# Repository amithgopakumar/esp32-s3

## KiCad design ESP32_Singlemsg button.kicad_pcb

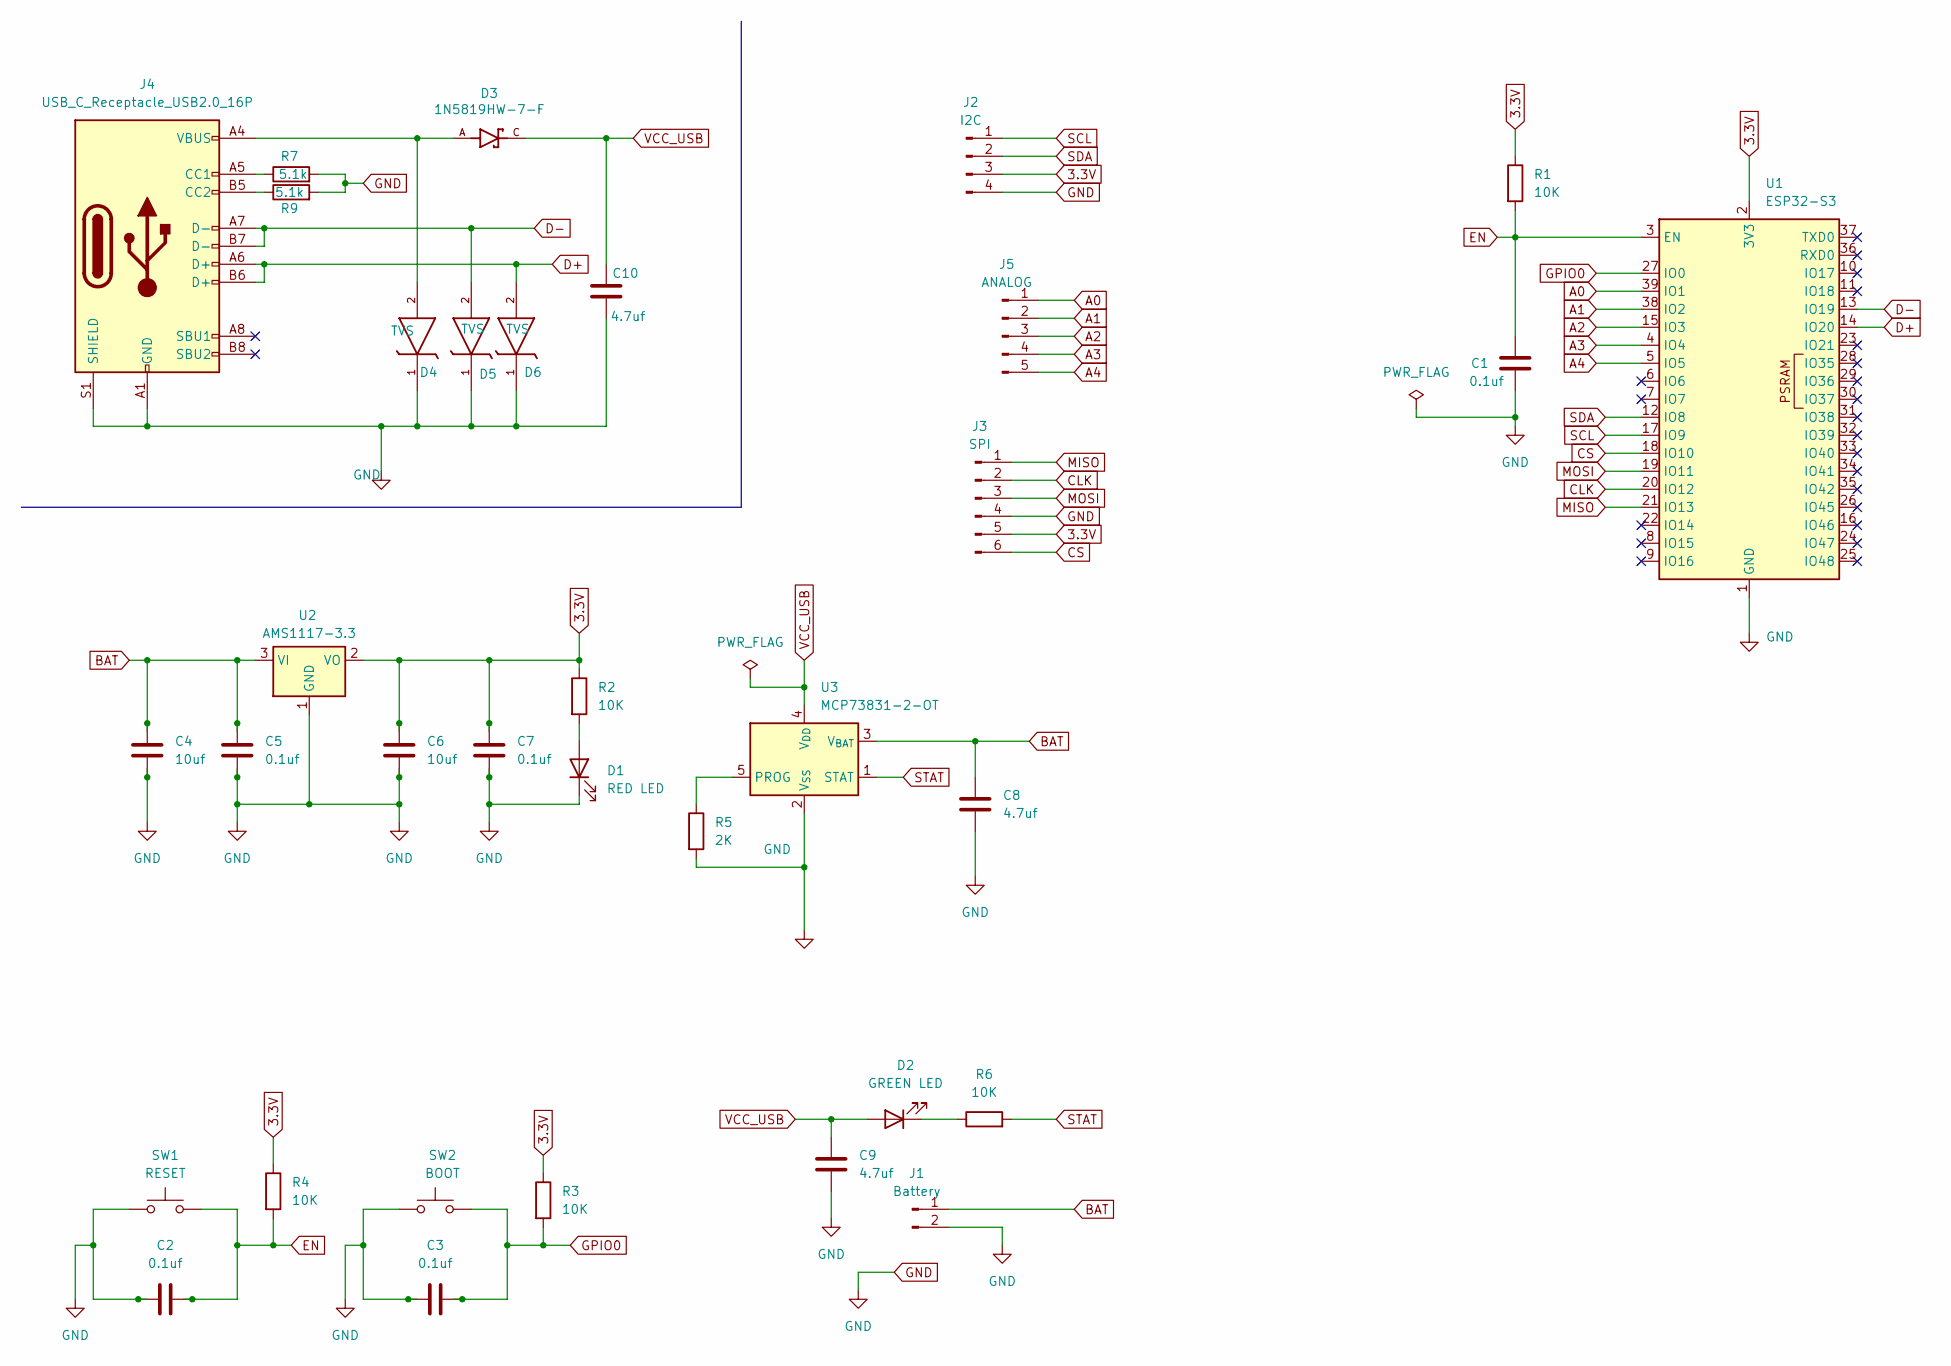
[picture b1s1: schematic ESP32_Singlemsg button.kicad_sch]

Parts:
C1, C2, C3, C5, C7: 0.1uf; C_1206_3216Metric
C4, C6: 10uf; C_1206_3216Metric
C8, C9, C10: 4.7uf; C_1206_3216Metric
D1: RED LED; LED_1206_3216Metric
D2: GREEN LED; LED_1206_3216Metric
D3: 1N5819HW-7-F; SOD3715X145N; PARTREV 18-2
D4, D5, D6: TVS; SMBJ5.0A; MANUFACTURER_PART_NUMBER SMBJ5.0CA
J1: Battery; JST_EH_S2B-EH_1x02_P2.50mm_Horizontal
J2: I2C; JST_EH_B4B-EH-A_1x04_P2.50mm_Vertical
J3: SPI; JST_EH_B6B-EH-A_1x06_P2.50mm_Vertical
J4: USB_C_Receptacle_USB2.0_16P; USB_C_Receptacle_GCT_USB4085
J5: ANALOG; JST_EH_B5B-EH-A_1x05_P2.50mm_Vertical
R1, R2, R3, R4, R6: 10K; R_1206_3216Metric_Pad1.30x1.75mm_HandSolder
R5: 2K; R_1206_3216Metric_Pad1.30x1.75mm_HandSolder
R7, R9: 5.1k; R_1206_3216Metric_Pad1.30x1.75mm_HandSolder
SW1: RESET; SW_Tactile_SPST_NO_Straight_CK_PTS636Sx25SMTRLFS
SW2: BOOT; SW_Tactile_SPST_NO_Straight_CK_PTS636Sx25SMTRLFS
U1: ESP32-S3; ESP32-S3-WROOM-1
U2: AMS1117-3.3; SOT-223-3_TabPin2
U3: MCP73831-2-OT; SOT-23-5

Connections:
3.3V: C6.1, C7.1, J2.3, J3.5, R1.1, R2.1, R3.1, R4.1, U1.2 (3V3), U2.2 (VO)
A0: J5.1, U1.39 (IO1)
A1: J5.2, U1.38 (IO2)
A2: J5.3, U1.15 (IO3)
A3: J5.4, U1.4 (IO4)
A4: J5.5, U1.5 (IO5)
BAT: C4.1, C5.1, C8.1, J1.1, U2.3 (VI), U3.3 (V_{BAT})
CLK: J3.2, U1.20 (IO12)
CS: J3.6, U1.18 (IO10)
D+: D6.2, J4.A6 (D+), J4.B6 (D+), U1.14 (IO20)
D-: D5.2, J4.A7 (D-), J4.B7 (D-), U1.13 (IO19)
EN: C1.1, C2.2, R1.2, R4.2, SW1.2, U1.3 (EN)
GND: C1.2, C2.1, C3.1, C4.2, C5.2, C6.2, C7.2, C8.2, C9.2, C10.2, D1.1 (K), D4.1, D5.1, D6.1, J1.2, J2.4, J3.4, J4.A1 (GND), J4.A12 (GND), J4.B1 (GND), J4.B12 (GND), J4.S1 (SHIELD), R5.2, R7.2, R9.2, SW1.1, SW2.1, U1.1 (GND), U1.40 (GND), U1.41 (GND), U2.1 (GND), U3.2 (V_{SS})
GPIO0: C3.2, R3.2, SW2.2, U1.27 (IO0)
MISO: J3.1, U1.21 (IO13)
MOSI: J3.3, U1.19 (IO11)
unnamed: D1.2 (A), R2.2
unnamed: D2.1 (K), R6.1
unnamed: D3.A, D4.2, J4.A4 (VBUS), J4.A9 (VBUS), J4.B4 (VBUS), J4.B9 (VBUS)
unnamed: J4.A5 (CC1), R7.1
unnamed: J4.B5 (CC2), R9.1
unnamed: R5.1, U3.5 (PROG)
SCL: J2.1, U1.17 (IO9)
SDA: J2.2, U1.12 (IO8)
STAT: R6.2, U3.1 (STAT)
VCC_USB: C9.1, C10.1, D2.2 (A), D3.C, U3.4 (V_{DD})

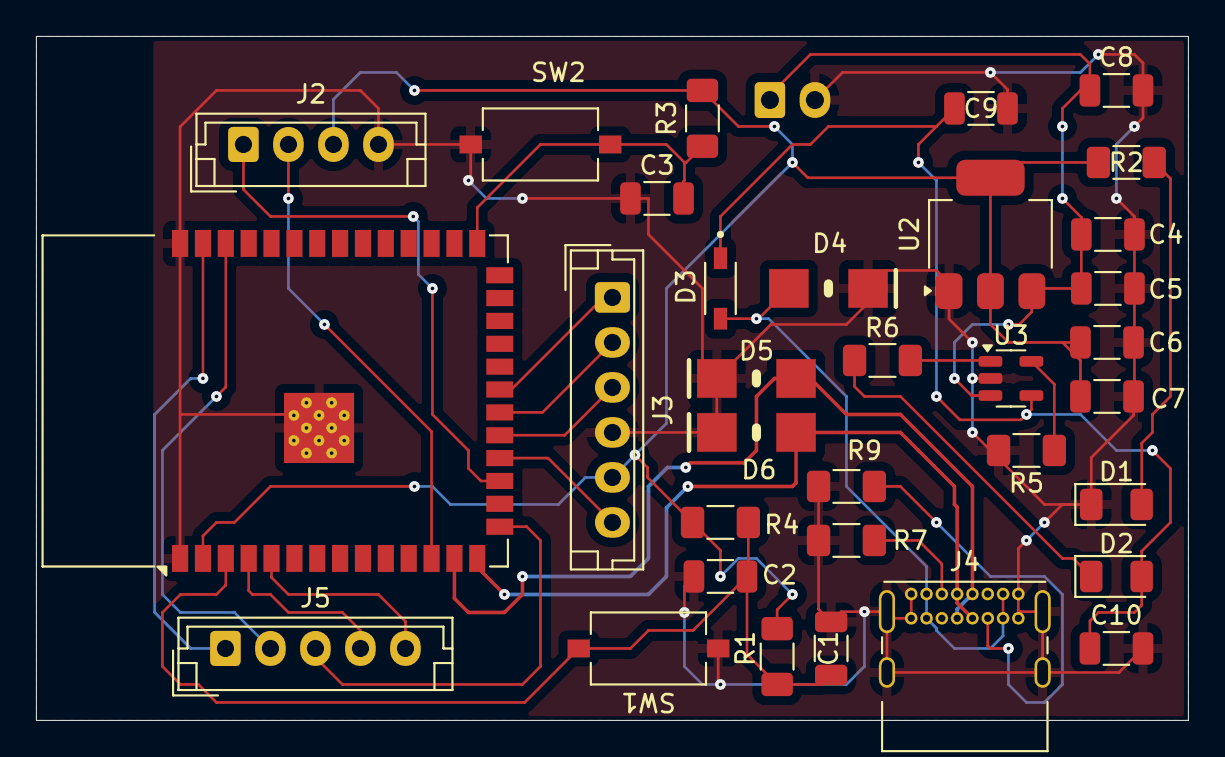
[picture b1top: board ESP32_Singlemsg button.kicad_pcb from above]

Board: 2 copper layers, 64.0 x 38.0 mm, 34 parts (1 on the bottom side), 26 nets.

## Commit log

2024-11-13 first update
2024-11-14 added silkscreen, ground plane cleaned up interfereing silkscreen note: there is two pullups for en pin drc and erc cleaned up
2024-11-14 Removed locks
